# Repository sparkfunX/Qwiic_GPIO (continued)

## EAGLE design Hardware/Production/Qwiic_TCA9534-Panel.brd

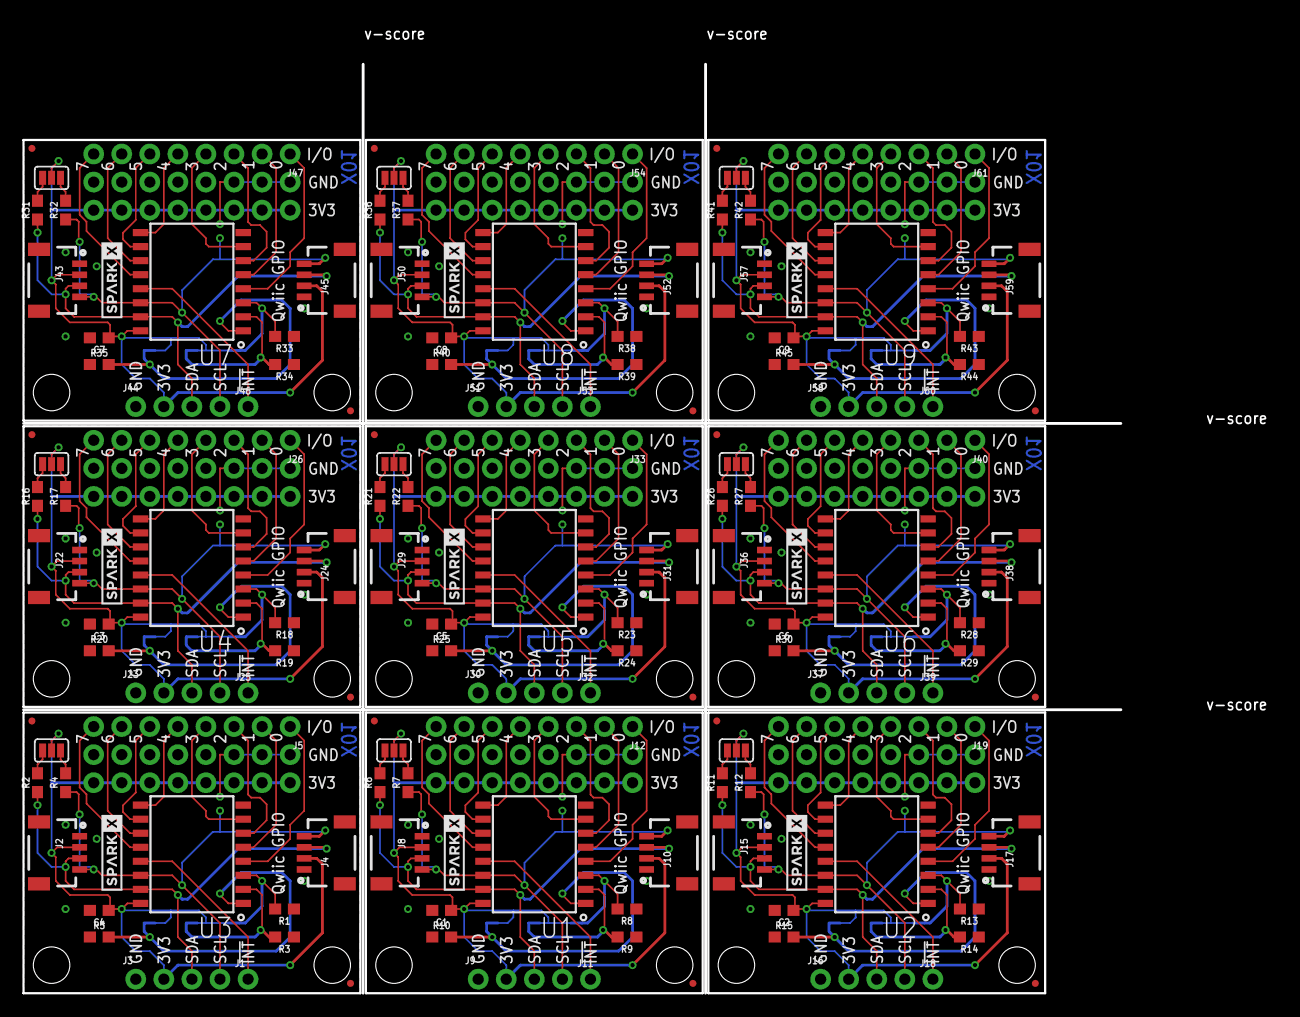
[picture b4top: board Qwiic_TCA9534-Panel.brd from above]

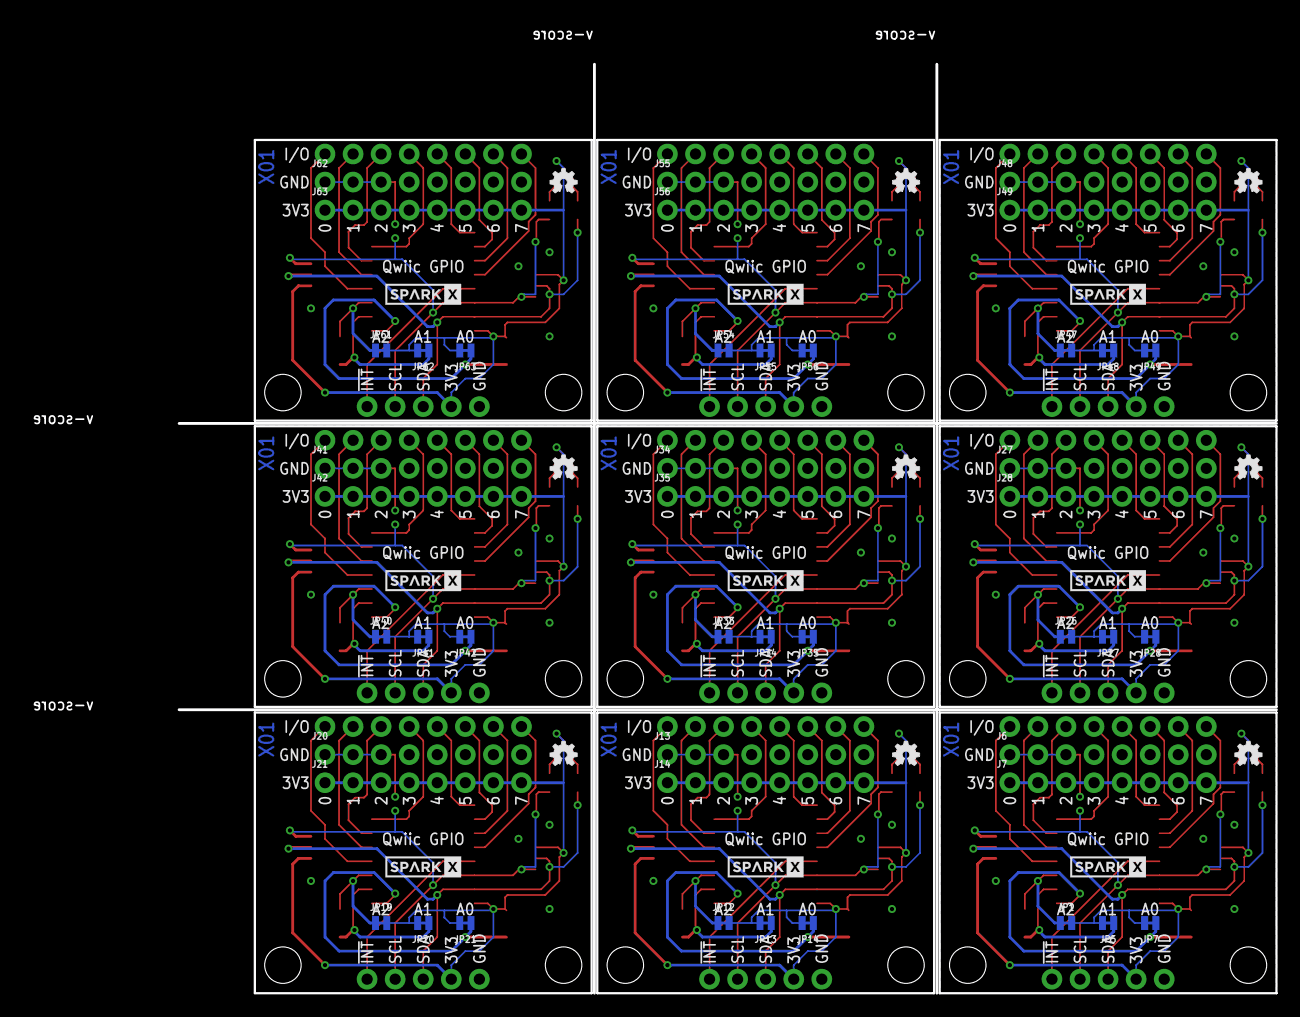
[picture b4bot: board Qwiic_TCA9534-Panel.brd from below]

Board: 2 copper layers, 113.4 x 87.8 mm, 225 parts (63 on the bottom side), 162 nets.

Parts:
C1, C2, C3, C4, C5, C6, C7, C8, C9: 0.1uF; 0603
J1, J11, J18, J25, J32, J39, J46, J53, J60: 1X01_NO_SILK
J2, J4, J8, J10, J15, J17, J22, J24, J29, J31, J36, J38, J43, J45, J50, J52, J57, J59: SMD; 1X04_1MM_RA
J3, J9, J16, J23, J30, J37, J44, J51, J58: PTH; 1X04_NO_SILK
J5, J6, J7, J12, J13, J14, J19, J20, J21, J26, J27, J28, J33, J34, J35, J40, J41, J42, J47, J48, J49, J54, J55, J56, J61, J62, J63: 1X08_NO_SILK
JP1, JP5, JP7, JP12, JP13, JP14, JP19, JP20, JP21, JP26, JP27, JP28, JP33, JP34, JP35, JP40, JP41, JP42, JP47, JP48, JP49, JP54, JP55, JP56, JP61, JP62, JP63: JUMPER-SMT_2_NC_TRACE_NO-SILK; SMT-JUMPER_2_NC_TRACE_NO-SILK
JP2, JP6, JP10, JP11, JP17, JP18, JP24, JP25, JP31, JP32, JP38, JP39, JP45, JP46, JP52, JP53, JP59, JP60: FIDUCIALUFIDUCIAL; MICRO-FIDUCIAL
JP3, JP4, JP8, JP9, JP15, JP16, JP22, JP23, JP29, JP30, JP36, JP37, JP43, JP44, JP50, JP51, JP57, JP58: STAND-OFF
LOGO1, LOGO2, LOGO3, LOGO4, LOGO5, LOGO6, LOGO7, LOGO8, LOGO9: OSHW-LOGOMINI; OSHW-LOGO-MINI
R1, R3, R5, R8, R9, R10, R13, R14, R15, R18, R19, R20, R23, R24, R25, R28, R29, R30, R33, R34, R35, R38, R39, R40, R43, R44, R45: 10k; 0603
R2, R4, R6, R7, R11, R12, R16, R17, R21, R22, R26, R27, R31, R32, R36, R37, R41, R42: 2.2k; 0603
SJ1, SJ2, SJ3, SJ4, SJ5, SJ6, SJ7, SJ8, SJ9: SMT-JUMPER-_3-2-NC-PASTE_TALL; SMT-JUMPER_3-2-NC-PASTE_SILK_TALLER_A
U1, U2, U3, U4, U5, U6, U7, U8, U9: TCA9534U; 16SOIC
U$1, U$2, U$3, U$4, U$5, U$6, U$7, U$8, U$9, U$10, U$11, U$12, U$13, U$14, U$15, U$16, U$17, U$18: SPARKX-LOGO3; SPARKX-SMALL

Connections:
3.3V: C4.1, J2.2, J3.2, J4.2, J7.1, J7.2, J7.3, J7.4, J7.5, J7.6, J7.7, J7.8, JP1.2, JP5.2, JP7.2, SJ5.2, U3.16
3.3V1: C1.1, J8.2, J9.2, J10.2, J14.1, J14.2, J14.3, J14.4, J14.5, J14.6, J14.7, J14.8, JP12.2, JP13.2, JP14.2, SJ1.2, U1.16
3.3V2: C2.1, J15.2, J16.2, J17.2, J21.1, J21.2, J21.3, J21.4, J21.5, J21.6, J21.7, J21.8, JP19.2, JP20.2, JP21.2, SJ2.2, U2.16
3.3V3: C3.1, J22.2, J23.2, J24.2, J28.1, J28.2, J28.3, J28.4, J28.5, J28.6, J28.7, J28.8, JP26.2, JP27.2, JP28.2, SJ3.2, U4.16
3.3V4: C5.1, J29.2, J30.2, J31.2, J35.1, J35.2, J35.3, J35.4, J35.5, J35.6, J35.7, J35.8, JP33.2, JP34.2, JP35.2, SJ4.2, U5.16
3.3V5: C6.1, J36.2, J37.2, J38.2, J42.1, J42.2, J42.3, J42.4, J42.5, J42.6, J42.7, J42.8, JP40.2, JP41.2, JP42.2, SJ6.2, U6.16
3.3V6: C7.1, J43.2, J44.2, J45.2, J49.1, J49.2, J49.3, J49.4, J49.5, J49.6, J49.7, J49.8, JP47.2, JP48.2, JP49.2, SJ7.2, U7.16
3.3V7: C8.1, J50.2, J51.2, J52.2, J56.1, J56.2, J56.3, J56.4, J56.5, J56.6, J56.7, J56.8, JP54.2, JP55.2, JP56.2, SJ8.2, U8.16
3.3V8: C9.1, J57.2, J58.2, J59.2, J63.1, J63.2, J63.3, J63.4, J63.5, J63.6, J63.7, J63.8, JP61.2, JP62.2, JP63.2, SJ9.2, U9.16
!INT: J1.1, U3.13
!INT1: J11.1, U1.13
!INT2: J18.1, U2.13
!INT3: J25.1, U4.13
!INT4: J32.1, U5.13
!INT5: J39.1, U6.13
!INT6: J46.1, U7.13
!INT7: J53.1, U8.13
!INT8: J60.1, U9.13
A0: JP7.1, R5.2, U3.1
A1: JP5.1, R3.2, U3.2
A2: JP1.1, R1.2, U3.3
A3: JP14.1, R10.2, U1.1
A4: JP13.1, R9.2, U1.2
A5: JP12.1, R8.2, U1.3
A6: JP21.1, R15.2, U2.1
A7: JP20.1, R14.2, U2.2
A8: JP19.1, R13.2, U2.3
A9: JP28.1, R20.2, U4.1
A10: JP27.1, R19.2, U4.2
A11: JP26.1, R18.2, U4.3
A12: JP35.1, R25.2, U5.1
A13: JP34.1, R24.2, U5.2
A14: JP33.1, R23.2, U5.3
A15: JP42.1, R30.2, U6.1
A16: JP41.1, R29.2, U6.2
A17: JP40.1, R28.2, U6.3
A18: JP49.1, R35.2, U7.1
A19: JP48.1, R34.2, U7.2
A20: JP47.1, R33.2, U7.3
A21: JP56.1, R40.2, U8.1
A22: JP55.1, R39.2, U8.2
A23: JP54.1, R38.2, U8.3
A24: JP63.1, R45.2, U9.1
A25: JP62.1, R44.2, U9.2
A26: JP61.1, R43.2, U9.3
GND: C4.2, J2.1, J3.1, J4.1, J6.1, J6.2, J6.3, J6.4, J6.5, J6.6, J6.7, J6.8, R1.1, R3.1, R5.1, U3.8
GND1: C1.2, J8.1, J9.1, J10.1, J13.1, J13.2, J13.3, J13.4, J13.5, J13.6, J13.7, J13.8, R8.1, R9.1, R10.1, U1.8
GND2: C2.2, J15.1, J16.1, J17.1, J20.1, J20.2, J20.3, J20.4, J20.5, J20.6, J20.7, J20.8, R13.1, R14.1, R15.1, U2.8
GND3: C3.2, J22.1, J23.1, J24.1, J27.1, J27.2, J27.3, J27.4, J27.5, J27.6, J27.7, J27.8, R18.1, R19.1, R20.1, U4.8
GND4: C5.2, J29.1, J30.1, J31.1, J34.1, J34.2, J34.3, J34.4, J34.5, J34.6, J34.7, J34.8, R23.1, R24.1, R25.1, U5.8
GND5: C6.2, J36.1, J37.1, J38.1, J41.1, J41.2, J41.3, J41.4, J41.5, J41.6, J41.7, J41.8, R28.1, R29.1, R30.1, U6.8
GND6: C7.2, J43.1, J44.1, J45.1, J48.1, J48.2, J48.3, J48.4, J48.5, J48.6, J48.7, J48.8, R33.1, R34.1, R35.1, U7.8
GND7: C8.2, J50.1, J51.1, J52.1, J55.1, J55.2, J55.3, J55.4, J55.5, J55.6, J55.7, J55.8, R38.1, R39.1, R40.1, U8.8
GND8: C9.2, J57.1, J58.1, J59.1, J62.1, J62.2, J62.3, J62.4, J62.5, J62.6, J62.7, J62.8, R43.1, R44.1, R45.1, U9.8
P0: J5.1, U3.4
P1: J5.2, U3.5
P2: J5.3, U3.6
P3: J5.4, U3.7
P4: J5.5, U3.9
P5: J5.6, U3.10
P6: J5.7, U3.11
P7: J5.8, U3.12
P8: J12.1, U1.4
P9: J12.3, U1.6
P10: J12.4, U1.7
P11: J12.5, U1.9
P12: J12.6, U1.10
P13: J12.7, U1.11
P14: J12.8, U1.12
P15: J12.2, U1.5
P16: J19.1, U2.4
P17: J19.3, U2.6
P18: J19.4, U2.7
P19: J19.5, U2.9
P20: J19.6, U2.10
P21: J19.7, U2.11
P22: J19.8, U2.12
P23: J19.2, U2.5
P24: J26.1, U4.4
P25: J26.3, U4.6
P26: J26.4, U4.7
P27: J26.5, U4.9
P28: J26.6, U4.10
P29: J26.7, U4.11
P30: J26.8, U4.12
P31: J26.2, U4.5
P32: J33.1, U5.4
P33: J33.3, U5.6
P34: J33.4, U5.7
P35: J33.5, U5.9
P36: J33.6, U5.10
P37: J33.7, U5.11
P38: J33.8, U5.12
P39: J33.2, U5.5
P40: J40.1, U6.4
P41: J40.3, U6.6
P42: J40.4, U6.7
P43: J40.5, U6.9
P44: J40.6, U6.10
P45: J40.7, U6.11
P46: J40.8, U6.12
P47: J40.2, U6.5
P48: J47.1, U7.4
P49: J47.3, U7.6
P50: J47.4, U7.7
P51: J47.5, U7.9
P52: J47.6, U7.10
P53: J47.7, U7.11
P54: J47.8, U7.12
P55: J47.2, U7.5
P56: J54.1, U8.4
P57: J54.3, U8.6
P58: J54.4, U8.7
P59: J54.5, U8.9
P60: J54.6, U8.10
P61: J54.7, U8.11
P62: J54.8, U8.12
P63: J54.2, U8.5
P64: J61.1, U9.4
P65: J61.3, U9.6
P66: J61.4, U9.7
P67: J61.5, U9.9
P68: J61.6, U9.10
P69: J61.7, U9.11
P70: J61.8, U9.12
P71: J61.2, U9.5
SCL: J2.4, J3.4, J4.4, R4.1, U3.14
SCL1: J8.4, J9.4, J10.4, R7.1, U1.14
SCL2: J15.4, J16.4, J17.4, R12.1, U2.14
SCL3: J22.4, J23.4, J24.4, R17.1, U4.14
SCL4: J29.4, J30.4, J31.4, R22.1, U5.14
SCL5: J36.4, J37.4, J38.4, R27.1, U6.14
SCL6: J43.4, J44.4, J45.4, R32.1, U7.14
SCL7: J50.4, J51.4, J52.4, R37.1, U8.14
SCL8: J57.4, J58.4, J59.4, R42.1, U9.14
SCL_PU1: R2.2, SJ5.1
SCL_PU2: R6.2, SJ1.1
SCL_PU3: R11.2, SJ2.1
SCL_PU4: R16.2, SJ3.1
SCL_PU5: R21.2, SJ4.1
SCL_PU6: R26.2, SJ6.1
SCL_PU7: R31.2, SJ7.1
SCL_PU8: R36.2, SJ8.1
SCL_PU9: R41.2, SJ9.1
SDA: J2.3, J3.3, J4.3, R2.1, U3.15
SDA1: J8.3, J9.3, J10.3, R6.1, U1.15
SDA2: J15.3, J16.3, J17.3, R11.1, U2.15
SDA3: J22.3, J23.3, J24.3, R16.1, U4.15
SDA4: J29.3, J30.3, J31.3, R21.1, U5.15
SDA5: J36.3, J37.3, J38.3, R26.1, U6.15
SDA6: J43.3, J44.3, J45.3, R31.1, U7.15
SDA7: J50.3, J51.3, J52.3, R36.1, U8.15
SDA8: J57.3, J58.3, J59.3, R41.1, U9.15
SDA_PU1: R4.2, SJ5.3
SDA_PU2: R7.2, SJ1.3
SDA_PU3: R12.2, SJ2.3
SDA_PU4: R17.2, SJ3.3
SDA_PU5: R22.2, SJ4.3
SDA_PU6: R27.2, SJ6.3
SDA_PU7: R32.2, SJ7.3
SDA_PU8: R37.2, SJ8.3
SDA_PU9: R42.2, SJ9.3

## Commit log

2018-02-26 initial
2018-02-26 fixing silk, move resistors from mounting holes
2018-02-26 partial route
2018-02-26 route complete
2018-04-11 starting to build out example 1
    example 1 is to set a pin on the expander as output or input, then set it as high or low. currently the setPinMode() function works, next is to make a 'digitalWrite' equivalent
2018-04-11 Example 1
    can now set the pinMode and the pinOutput as input, output, and set the output as high or low!
2018-04-11 trying to figure out the read
    button read works ok first do a mask
    value & PIN6
    THEN DO a shift. is this the best way to do that?
2018-04-12 basic functionality
    can set a pin as input output
    can read inputs
    can set output as high or low
    it appears to be working well for pins 1 through 8!
    should probably think about making the silk screen and the coded pins match, ie there is no pin 8 but pin 7 and there is a pin0 in silk but not a pin0 in the code.
2018-04-17 made better examples
    trimmed the exmaples for writing and reading a gpio pin,
    need to do more testing for the interrupt example
2018-04-24 Updated the examples
    Cleaned up the examples, made the suggested changes from code review, implemented a way to identify which pins triggered the interrupt.
2018-04-24 added addresses
    cleaned up schematic and added addresses.
2020-01-29 Updated PCB with latch terminals and buzzard labels
2020-01-30 Fixed routing and silk issues. Ready to order rev X02
2020-01-30 Change silk to table
2020-01-30 Silkscreen
2020-01-31 Panel/production files
2020-02-19 Added missing product ID's
2020-02-28 Wrote test script for qwiic gpio units
2020-03-02 Got rid of old/non-relevant files, created .zip and schematic for product page, moved test sketch to hardware folder
2020-03-04 Changed readme
    From SparkFun to SparkX
2020-03-13 Added PWR LED, made labels larger
2020-03-13 Generated new panel file
2020-03-25 Re-generated schematic .pdf with PWR LED
2020-04-06 Update SKU for new version of board
